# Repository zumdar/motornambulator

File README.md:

# quadmotornambulator 

a collaboration between [pin](http://paulapin.net/) and [zumdar](https://freakylamps.com/) at [Electric Wonderland 2022](https://www.electric-wonderland.eu/)

motors are people too

this is a non-identity 4x motor record and playback machine based on [ralf schreiber](http://www.ralfschreiber.com/)'s pulse pattern workshop. specifically, we are taking the 'attiny85 record + play', multiplying it times 4,put it on a single sided PCB, and etching it!
ralf's original circuit and code found here: http://www.ralfschreiber.com/share/pulseandpatterns.html

code for the attiny can be found at ralfs website above 

# notes for recreation
included in this repo is the kicad files, graphics, and final svg and pdfs for making the transparency and board etch.

custom footprints were made to make the pads larger for easier etching and soldering. those footprints can be found in the included william_custom.pretty folder. 

# documentation

VIDEO!

we etched the board on site at EW2022! 

user interface parts of the circuit are on the top, the rest are soldered on the bottom

part of the setup for the performance on 8/10/2022

motor madness

# TODO's

- button debouncing -- lots of button glitches makes it so it doesnt always record
- graphics displaying play and record buttons on pcb
- use one microcontroller? get more outputs?

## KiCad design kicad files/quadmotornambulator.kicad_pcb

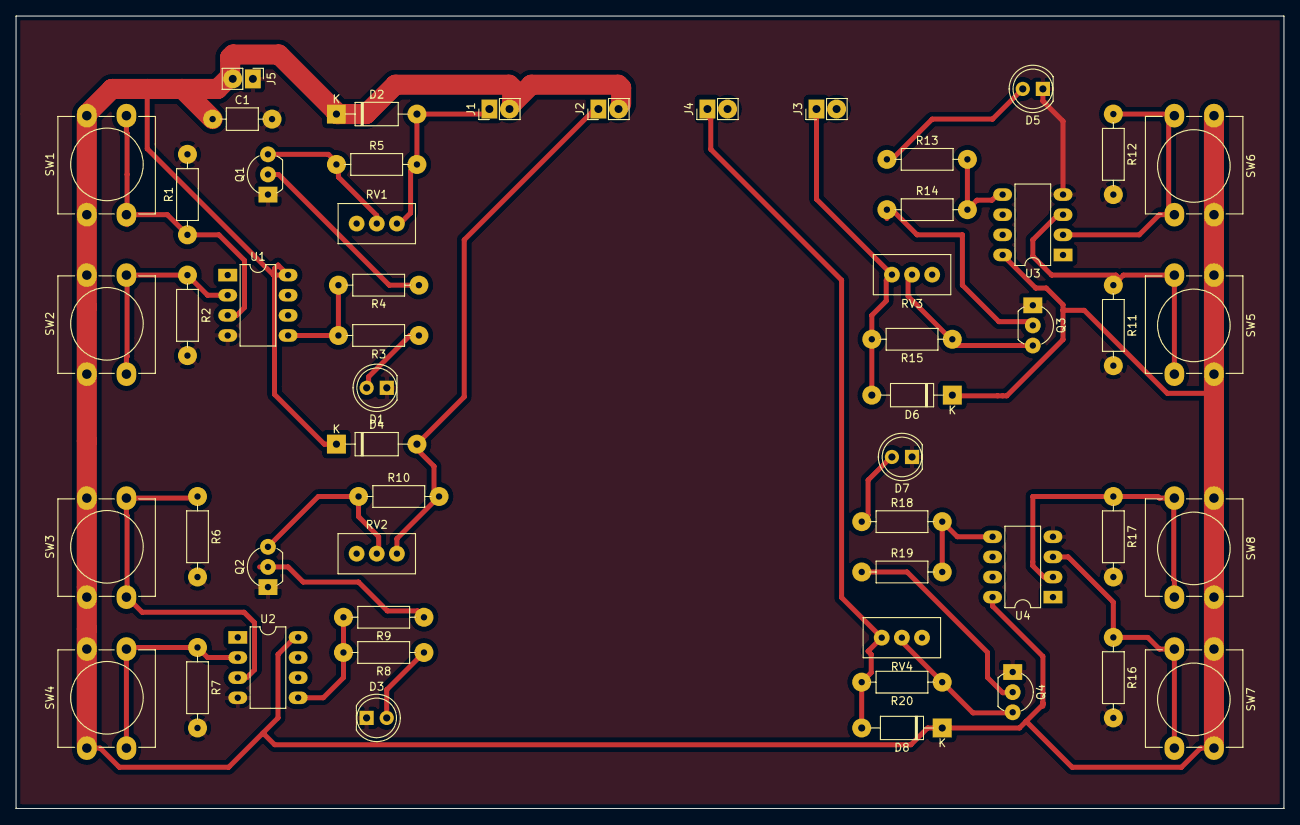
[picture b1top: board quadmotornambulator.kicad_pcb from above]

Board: 2 copper layers, 160.0 x 100.0 mm, 54 parts (0 on the bottom side), 30 nets.

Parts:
C1: 470u; C_Axial_L3.8mm_D2.6mm_P7.50mm_Horizontal_BIG
D1, D3, D5, D7: LED; LED_D5.0mm
D2, D4, D6, D8: 1n4841; D_A-405_P10.16mm_Horizontal_BIG
J1: motor1 out; PinHeader_1x02_P2.54mm_Vertical_BIG
J2: motor2 out; PinHeader_1x02_P2.54mm_Vertical_BIG
J3: motor3 out; PinHeader_1x02_P2.54mm_Vertical_BIG
J4: motor4 out; PinHeader_1x02_P2.54mm_Vertical_BIG
J5: Conn_01x02_Male; PinHeader_1x02_P2.54mm_Vertical_BIG
Q1, Q2, Q3, Q4: 2N3904; TO-92_Inline_Wide_BIG
R1, R2, R6, R7, R11, R12, R16, R17: 10k; R_Axial_DIN0207_L6.3mm_D2.5mm_P10.16mm_Horizontal_BIG
R3, R4, R8, R9, R13, R14, R18, R19: 1k; R_Axial_DIN0207_L6.3mm_D2.5mm_P10.16mm_Horizontal_BIG
R5, R10, R15, R20: 120; R_Axial_DIN0207_L6.3mm_D2.5mm_P10.16mm_Horizontal_BIG
RV1, RV2, RV3, RV4: 1k; Potentiometer_Bourns_3296W_Vertical_BIG
SW1, SW2, SW3, SW4, SW5, SW6, SW7, SW8: SW_SPST; SW_PUSH-12mm_Wuerth-430476085716
U1, U2, U3, U4: ATtiny85-20PU; DIP-8_W7.62mm_LongPads

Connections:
+5V: C1.1, D2.1, D4.1, D6.1, D8.1, J1.2, J2.2, J3.2, J4.2, J5.2, SW1.1, SW2.1, SW3.1, SW4.1, SW5.1, SW6.1, SW7.1, SW8.1, U1.8, U2.8, U3.8, U4.8
GND: C1.2, D1.1, D3.1, D5.1, D7.1, J5.1, Q1.1, Q2.1, Q3.1, Q4.1, R1.2, R2.2, R6.2, R7.2, R11.2, R12.2, R16.2, R17.2, U1.4, U2.4, U3.4, U4.4
unnamed: D1.2, R3.1
unnamed: D2.2, J1.1, R5.2, RV1.1
unnamed: D3.2, R8.1
unnamed: D4.2, J2.1, R10.2, RV2.1
unnamed: D5.2, R13.1
unnamed: D6.2, J3.1, R15.2, RV3.1
unnamed: D7.2, R18.1
unnamed: D8.2, J4.1, R20.2, RV4.1
unnamed: Q1.2, R4.1
unnamed: Q1.3, R5.1, RV1.2
unnamed: Q2.2, R9.1
unnamed: Q2.3, R10.1, RV2.2
unnamed: Q3.2, R14.1
unnamed: Q3.3, R15.1, RV3.2
unnamed: Q4.2, R19.1
unnamed: Q4.3, R20.1, RV4.2
unnamed: R1.1, SW1.2, U1.3
unnamed: R2.1, SW2.2, U1.2
unnamed: R3.2, R4.2, U1.5
unnamed: R6.1, SW3.2, U2.3
unnamed: R7.1, SW4.2, U2.2
unnamed: R8.2, R9.2, U2.5
unnamed: R11.1, SW5.2, U3.3
unnamed: R12.1, SW6.2, U3.2
unnamed: R13.2, R14.2, U3.5
unnamed: R16.1, SW7.2, U4.3
unnamed: R17.1, SW8.2, U4.2
unnamed: R18.2, R19.2, U4.5

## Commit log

2022-08-12 testing
2022-08-12 readme change
2022-08-12 adding photo
2022-08-12 asdf
